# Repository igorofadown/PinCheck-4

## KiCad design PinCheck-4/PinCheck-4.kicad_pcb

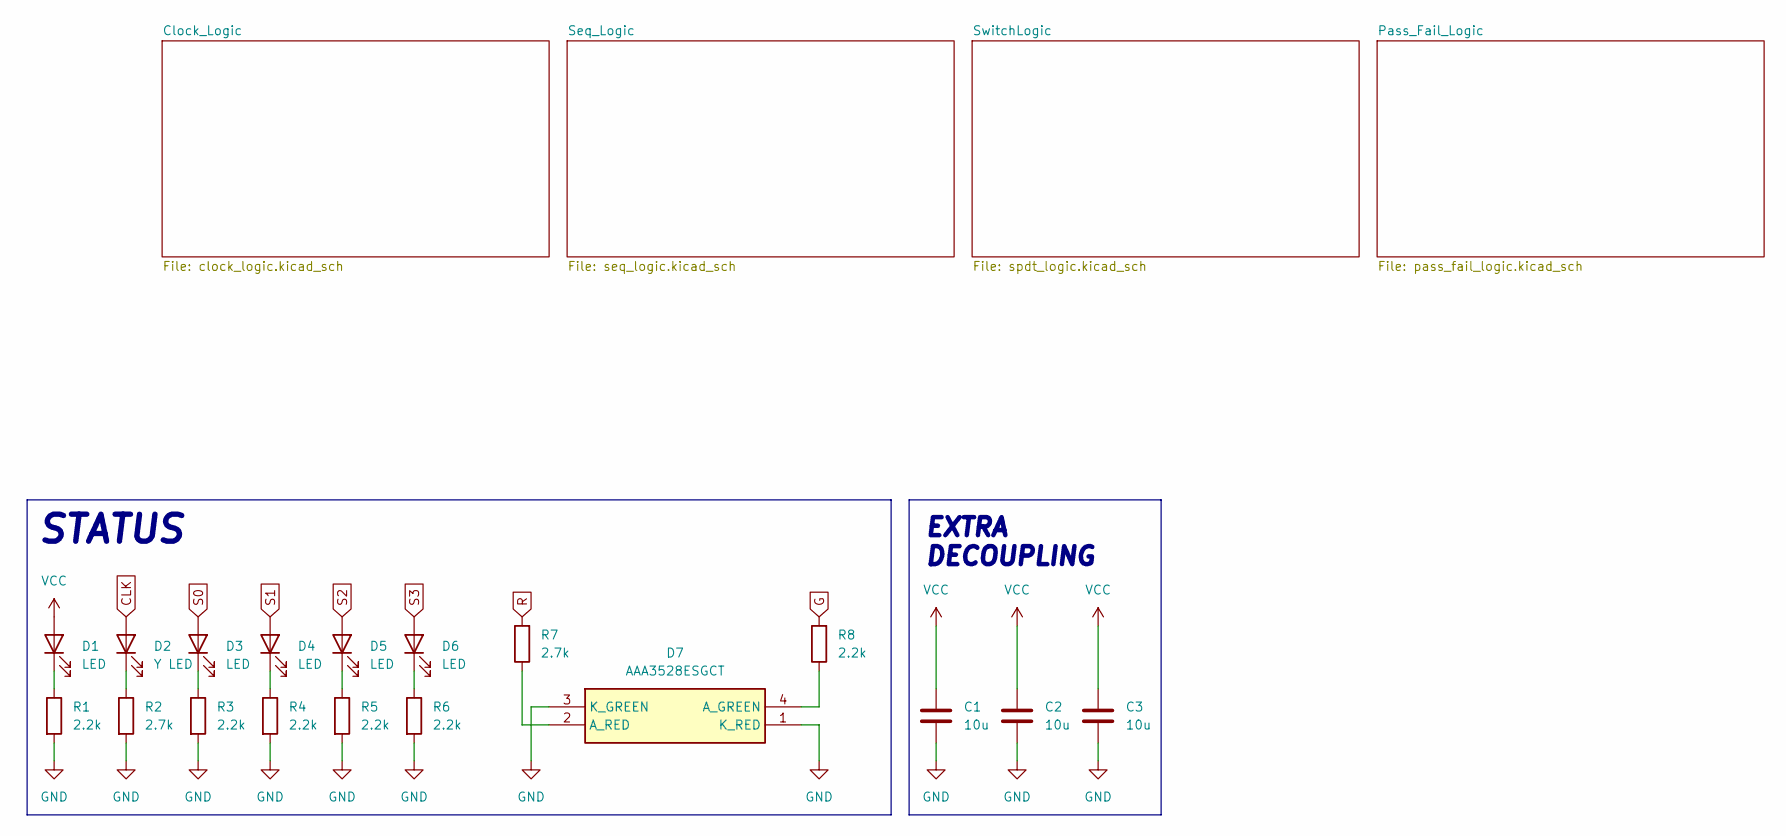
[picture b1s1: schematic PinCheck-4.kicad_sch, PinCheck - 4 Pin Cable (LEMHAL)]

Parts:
C1, C2, C3: 10u; C_0805_2012Metric
D1, D3, D4, D5, D6: LED; LED_0805_2012Metric; Manufacturer Part No KP-2012MGC
D2: Y LED; LED_0805_2012Metric; Manufacturer Part No KP-2012SECK
D7: AAA3528ESGCT; Manufacturer_Part_Number AAA3528ESGCT; Mouser Part Number 604-AAA3528ESGCT
R1, R3, R4, R5, R6, R8: 2.2k; R_0805_2012Metric; Manufacturer Part No MC01W080512K2
R2, R7: 2.7k; R_0805_2012Metric; Manufacturer Part No MCMR08X2701FTL

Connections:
CLK: D2.2 (A); also elsewhere on the board
G: R8.2; also elsewhere on the board
GND: C1.2, C2.2, C3.2, D7.1 (K_RED), D7.3 (K_GREEN), R1.2, R2.2, R3.2, R4.2, R5.2, R6.2; also elsewhere on the board
unnamed: D1.1 (K), R1.1
unnamed: D2.1 (K), R2.1
unnamed: D3.1 (K), R3.1
unnamed: D4.1 (K), R4.1
unnamed: D5.1 (K), R5.1
unnamed: D6.1 (K), R6.1
unnamed: D7.4 (A_GREEN), R8.1
unnamed: D7.2 (A_RED), R7.1
R: R7.2; also elsewhere on the board
S0: D3.2 (A); also elsewhere on the board
S1: D4.2 (A); also elsewhere on the board
S2: D5.2 (A); also elsewhere on the board
S3: D6.2 (A); also elsewhere on the board
VCC: C1.1, C2.1, C3.1, D1.2 (A); also elsewhere on the board

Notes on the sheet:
EXTRA DECOUPLING
STATUS

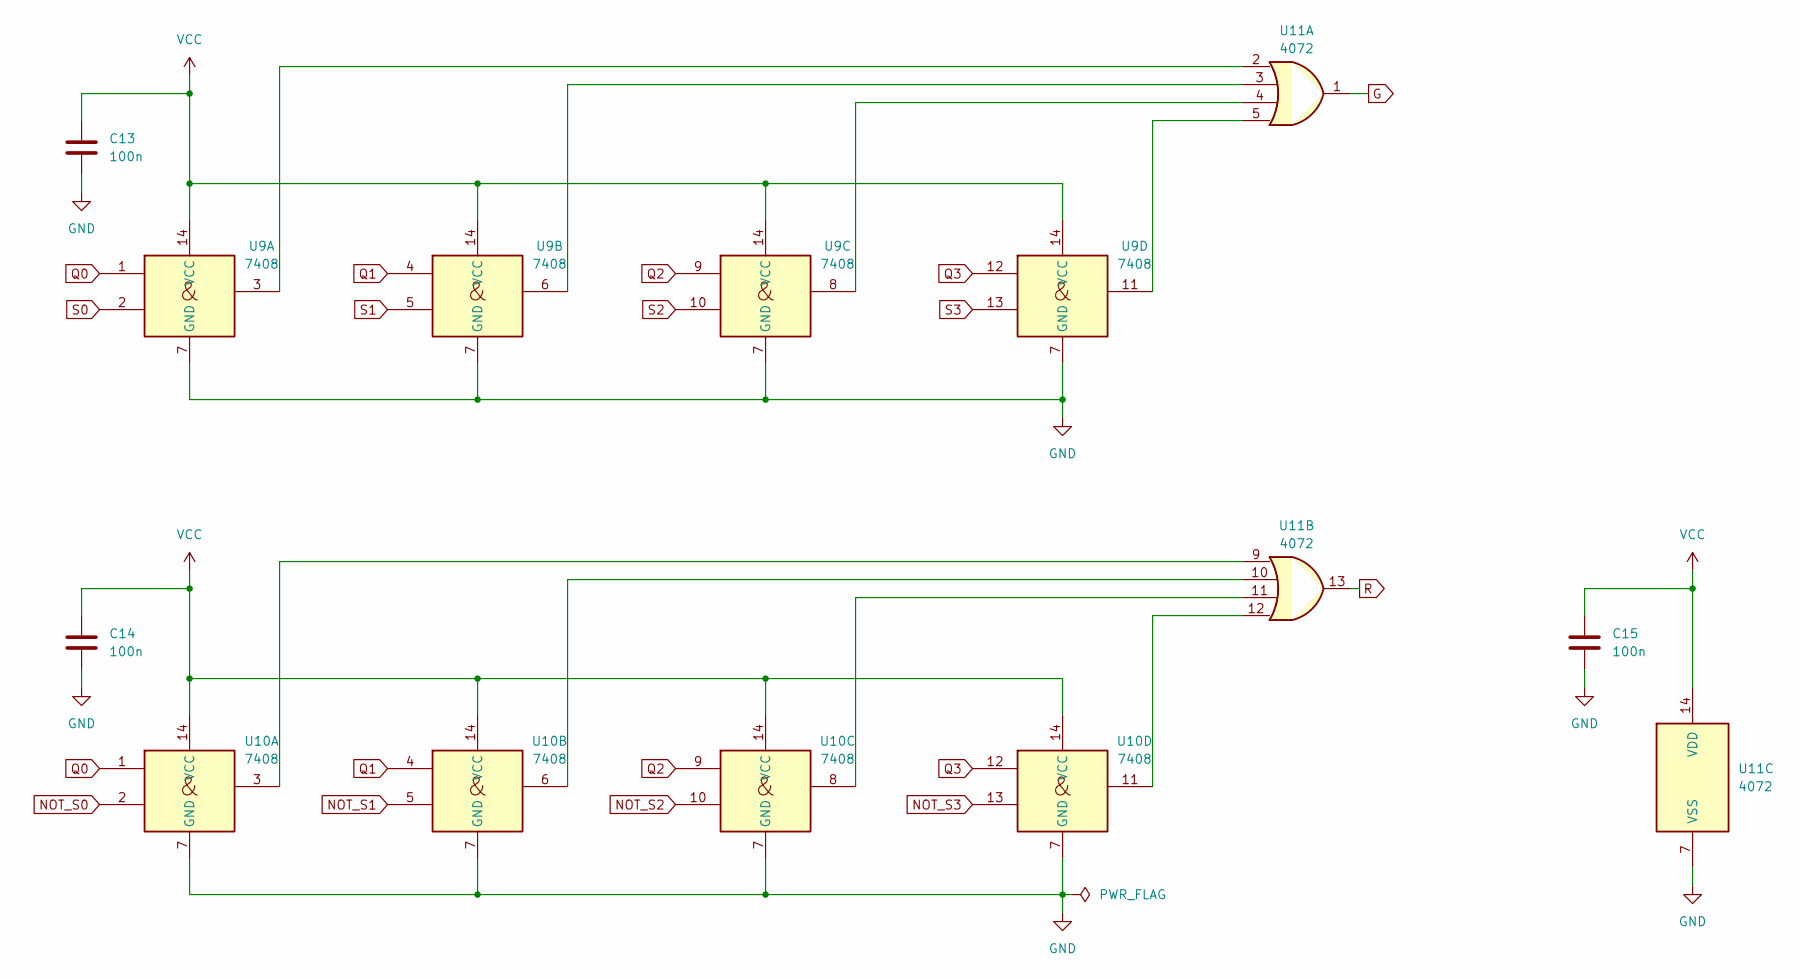
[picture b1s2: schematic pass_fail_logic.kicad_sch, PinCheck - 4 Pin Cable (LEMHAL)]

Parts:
C13, C14, C15: 100n; C_0805_2012Metric; Manufacturer Part No 0805B104K160CT
U9, U10: 7408; SOIC-14_3.9x8.7mm_P1.27mm; Manufacturer Part No 74HC08D
U11: 4072; SOIC-14_3.9x8.7mm_P1.27mm; Manufacturer Part No CD4072BM96

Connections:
G: U11.1; also elsewhere on the board
GND: C13.2, C14.2, C15.2, U9.7 (GND), U10.7 (GND), U11.7 (VSS); also elsewhere on the board
NOT_S0: U10.2; also elsewhere on the board
NOT_S1: U10.5; also elsewhere on the board
NOT_S2: U10.10; also elsewhere on the board
NOT_S3: U10.13; also elsewhere on the board
unnamed: U10.3, U11.9
unnamed: U10.6, U11.10
unnamed: U10.8, U11.11
unnamed: U10.11, U11.12
unnamed: U9.3, U11.2
unnamed: U9.6, U11.3
unnamed: U9.8, U11.4
unnamed: U9.11, U11.5
Q0: U9.1, U10.1; also elsewhere on the board
Q1: U9.4, U10.4; also elsewhere on the board
Q2: U9.9, U10.9; also elsewhere on the board
Q3: U9.12, U10.12; also elsewhere on the board
R: U11.13; also elsewhere on the board
S0: U9.2; also elsewhere on the board
S1: U9.5; also elsewhere on the board
S2: U9.10; also elsewhere on the board
S3: U9.13; also elsewhere on the board
VCC: C13.1, C14.1, C15.1, U9.14 (VCC), U10.14 (VCC), U11.14 (VDD); also elsewhere on the board

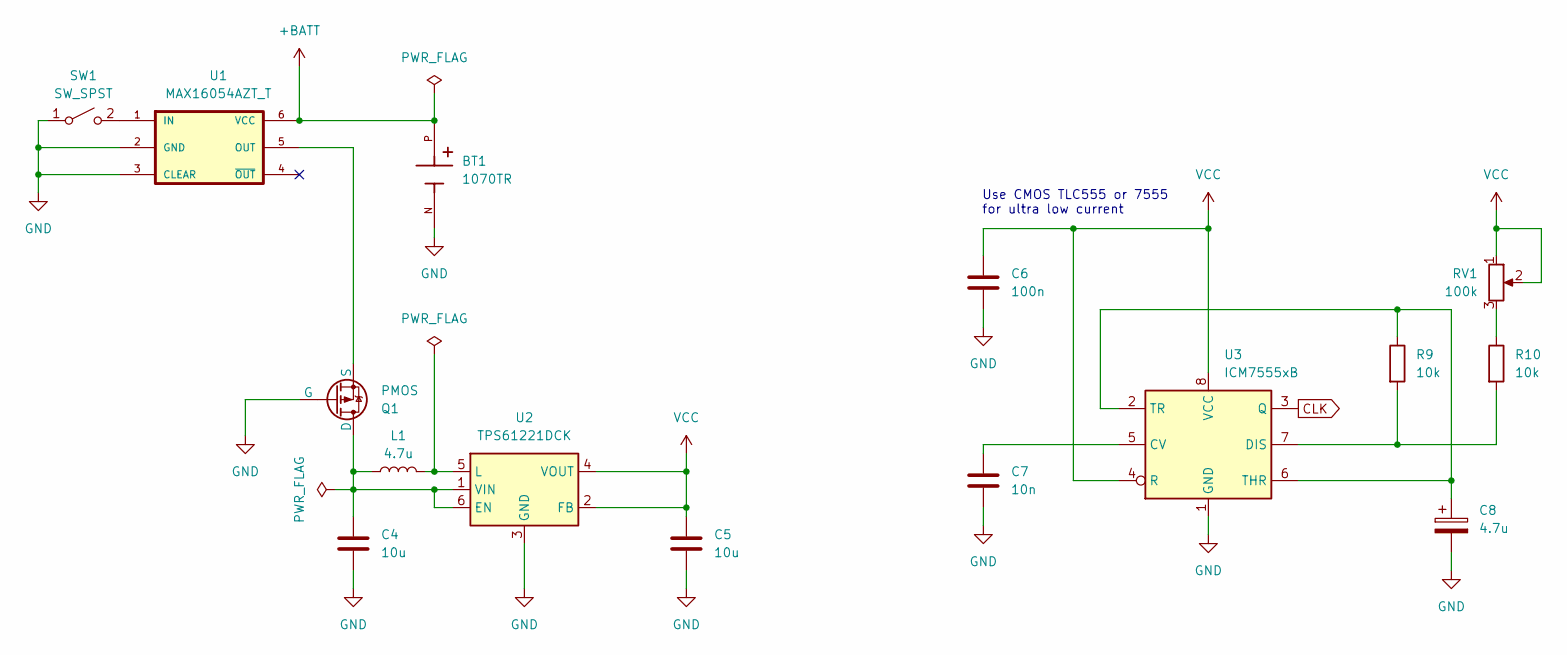
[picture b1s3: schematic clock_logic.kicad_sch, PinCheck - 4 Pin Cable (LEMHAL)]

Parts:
BT1: 1070TR; KEYSTONE_1070TR; PARTREV C
C4, C5: 10u; C_0805_2012Metric; Manufacturer Part No C2012X5R1C106M085AC
C6: 100n; C_0805_2012Metric; Manufacturer Part No 0805B104K160CT
C7: 10n; C_0805_2012Metric; Manufacturer Part No C0805S103K4RACTU
C8: 4.7u; CP_Elec_5x4.5; Manufacturer Part No EEE1EA4R7NR
L1: 4.7u; EPL3015472MLC; Manufacturer Part No EPL3015-472MLC
Q1: PMOS; SOT-323_SC-70; Manufacturer Part No AO3407A
R9, R10: 10k; R_0805_2012Metric; Manufacturer Part No CR0805-FX-1002ELF
RV1: 100k; Potentiometer_Bourns_3314G_Vertical; Manufacturer Part No 3314G-1-104E
SW1: SW_SPST; SW_SPST_PTS645Sx43SMTR92; Manufacturer Part No TS04-66-70-BK-160-SMT
U1: MAX16054AZT_T; TSOT-23-6_HandSoldering; Manufacturer Part No MAX16054AZT+T
U2: TPS61221DCK; Texas_R-PDSO-G6; Manufacturer Part No TPS61221DCKT
U3: ICM7555xB; SOIC-8_3.9x4.9mm_P1.27mm; Manufacturer Part No ICM7555ESA+T

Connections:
+BATT: BT1.P, U1.6 (VCC)
CLK: U3.3 (Q); also elsewhere on the board
GND: BT1.N, C4.2, C5.2, C6.2, C7.2, C8.2, Q1.1 (G), SW1.1 (A), U1.2 (GND), U1.3 (CLEAR), U2.3 (GND), U3.1 (GND); also elsewhere on the board
unnamed: C4.1, L1.1, Q1.3 (D), U2.1 (VIN), U2.6 (EN)
unnamed: Q1.2 (S), U1.5 (OUT)
unnamed: R10.1, RV1.3
unnamed: SW1.2 (B), U1.1 (IN)
unnamed: L1.2, U2.5 (L)
unnamed: C7.1, U3.5 (CV)
unnamed: R9.2, R10.2, U3.7 (DIS)
unnamed: C8.1, R9.1, U3.2 (TR), U3.6 (THR)
VCC: C5.1, C6.1, RV1.1, RV1.2, U2.2 (FB), U2.4 (VOUT), U3.4 (R), U3.8 (VCC); also elsewhere on the board

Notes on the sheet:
Use CMOS TLC555 or 7555 for ultra low current

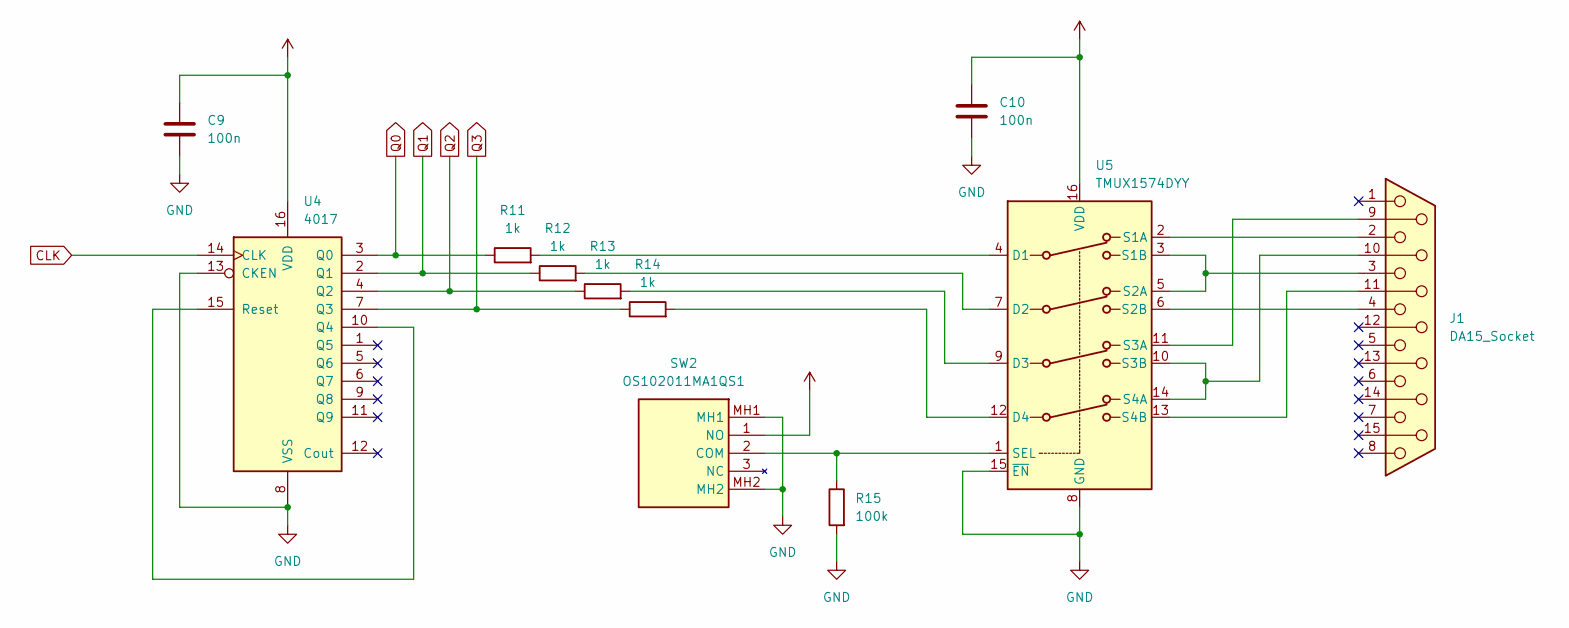
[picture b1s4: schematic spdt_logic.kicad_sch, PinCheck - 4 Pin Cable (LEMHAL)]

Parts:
C9, C10: 100n; C_0805_2012Metric; Manufacturer Part No 0805B104K160CT
J1: DA15_Socket; DSUB-15_Socket_Horizontal_P2.77x2.84mm_EdgePinOffset9.90mm_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; Manufacturer Part No MHDD15-F-T-B-S-R
R11, R12, R13, R14: 1k; R_0805_2012Metric; Manufacturer Part No MCMR08X1001FTL
R15: 100k; R_0805_2012Metric; Manufacturer Part No ERJP6WF1003V
SW2: OS102011MA1QS1; Manufacturer_Part_Number OS102011MA1QS1; Mouser Part Number N/A
U4: 4017; SOIC-16_3.9x9.9mm_P1.27mm; Manufacturer Part No CD4017BM96
U5: TMUX1574DYY; Texas_DYY0016A_TSOT-23-16_2x4.2mm_P0.5mm; Manufacturer Part No 4 Circuit IC Switch 2:1 4.5Ohm 16-SOT-2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

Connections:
CLK: U4.14 (CLK); also elsewhere on the board
GND: C9.2, C10.2, R15.2, SW2.MH1, SW2.MH2, U4.8 (VSS), U4.13 (CKEN), U5.8 (GND), U5.15 (~EN); also elsewhere on the board
unnamed: J1.9, U5.11 (S3A)
unnamed: J1.10, U5.10 (S3B), U5.14 (S4A)
unnamed: J1.11 (P111), U5.13 (S4B)
unnamed: R15.1, SW2.2 (COM), U5.1 (SEL)
unnamed: U4.10 (Q4), U4.15 (Reset)
unnamed: R11.2, U5.4 (D1)
unnamed: R12.2, U5.7 (D2)
unnamed: R13.2, U5.9 (D3)
unnamed: R14.2, U5.12 (D4)
unnamed: J1.2, U5.2 (S1A)
unnamed: J1.3, U5.3 (S1B), U5.5 (S2A)
unnamed: J1.4, U5.6 (S2B)
Q0: R11.1, U4.3 (Q0); also elsewhere on the board
Q1: R12.1, U4.2 (Q1); also elsewhere on the board
Q2: R13.1, U4.4 (Q2); also elsewhere on the board
Q3: R14.1, U4.7 (Q3); also elsewhere on the board
VCC: C9.1, C10.1, SW2.1 (NO), U4.16 (VDD), U5.16 (VDD); also elsewhere on the board

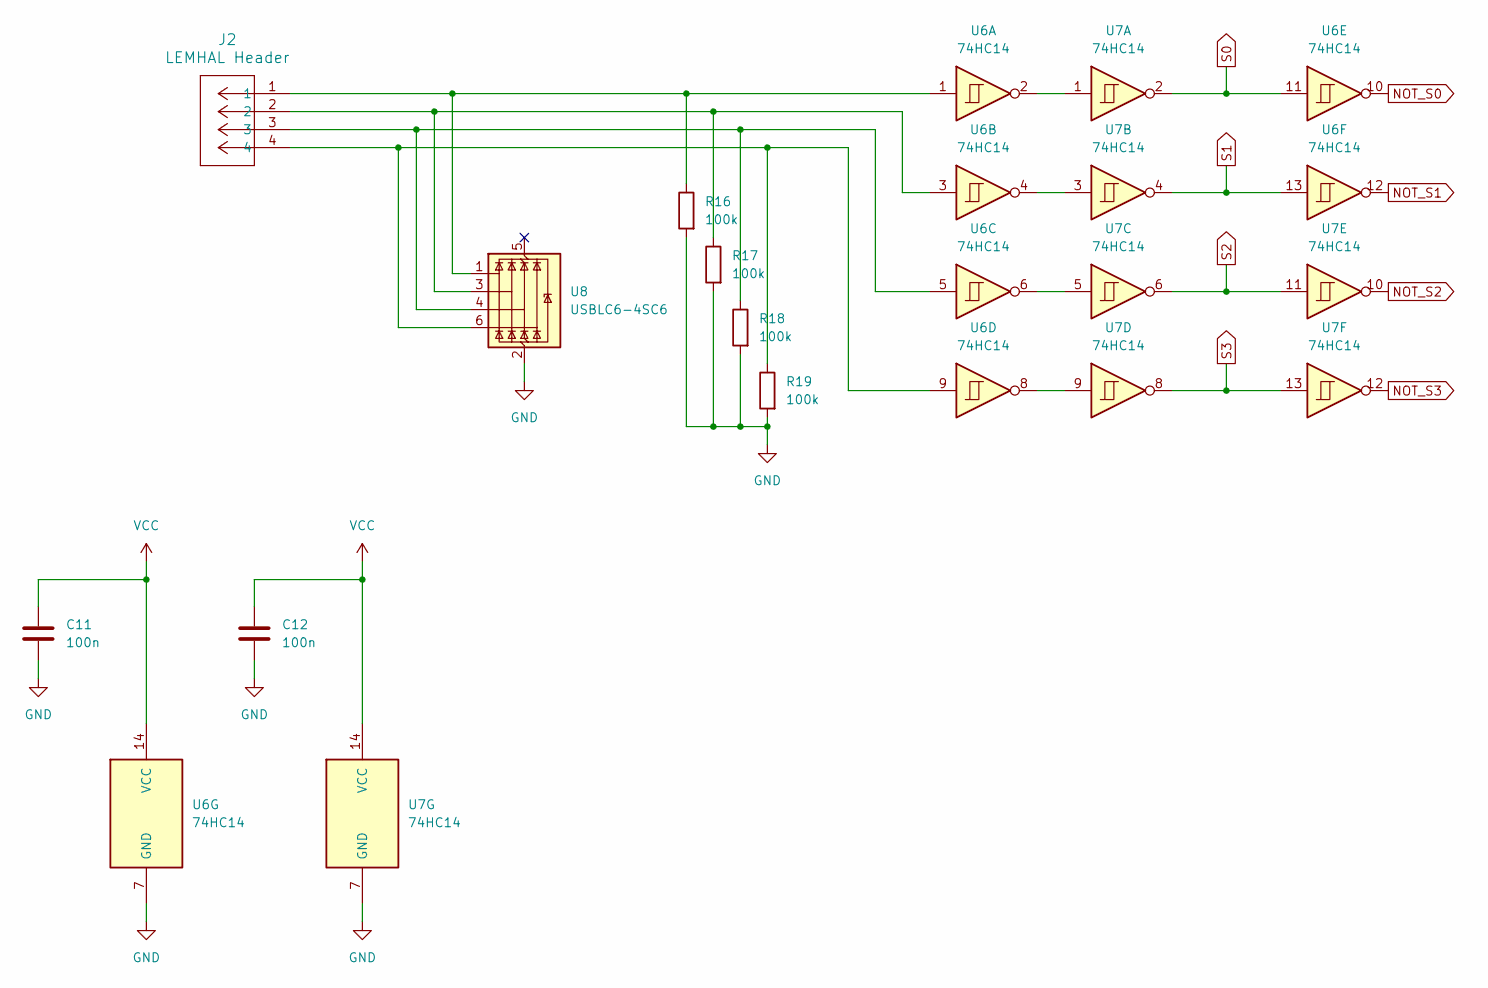
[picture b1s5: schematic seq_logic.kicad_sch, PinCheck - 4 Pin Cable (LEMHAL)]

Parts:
C11, C12: 100n; C_0805_2012Metric; Manufacturer Part No 0805B104K160CT
J2: LEMHAL Header; CONN_A-7478-04A_MOL; Manufacturer Part No 22-05-3041
R16, R17, R18, R19: 100k; R_0805_2012Metric; Manufacturer Part No ERJP6WF1003V
U6, U7: 74HC14; SOIC-14_3.9x8.7mm_P1.27mm; Manufacturer Part No 74HC14D
U8: USBLC6-4SC6; SOT-23-6; Manufacturer Part No USBLC6-4SC6

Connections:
GND: C11.2, C12.2, R16.2, R17.2, R18.2, R19.2, U6.7 (GND), U7.7 (GND), U8.2 (GND); also elsewhere on the board
NOT_S0: U6.10; also elsewhere on the board
NOT_S1: U6.12; also elsewhere on the board
NOT_S2: U7.10; also elsewhere on the board
NOT_S3: U7.12; also elsewhere on the board
unnamed: U6.2, U7.1
unnamed: U6.4, U7.3
unnamed: U6.6, U7.5
unnamed: U6.8, U7.9
unnamed: J2.1, R16.1, U6.1, U8.1 (I/O1)
unnamed: J2.2, R17.1, U6.3, U8.3 (I/O2)
unnamed: J2.3, R18.1, U6.5, U8.4 (I/O3)
unnamed: J2.4, R19.1, U6.9, U8.6 (I/O4)
S0: U6.11, U7.2; also elsewhere on the board
S1: U6.13, U7.4; also elsewhere on the board
S2: U7.6, U7.11; also elsewhere on the board
S3: U7.8, U7.13; also elsewhere on the board
VCC: C11.1, C12.1, U6.14 (VCC), U7.14 (VCC); also elsewhere on the board

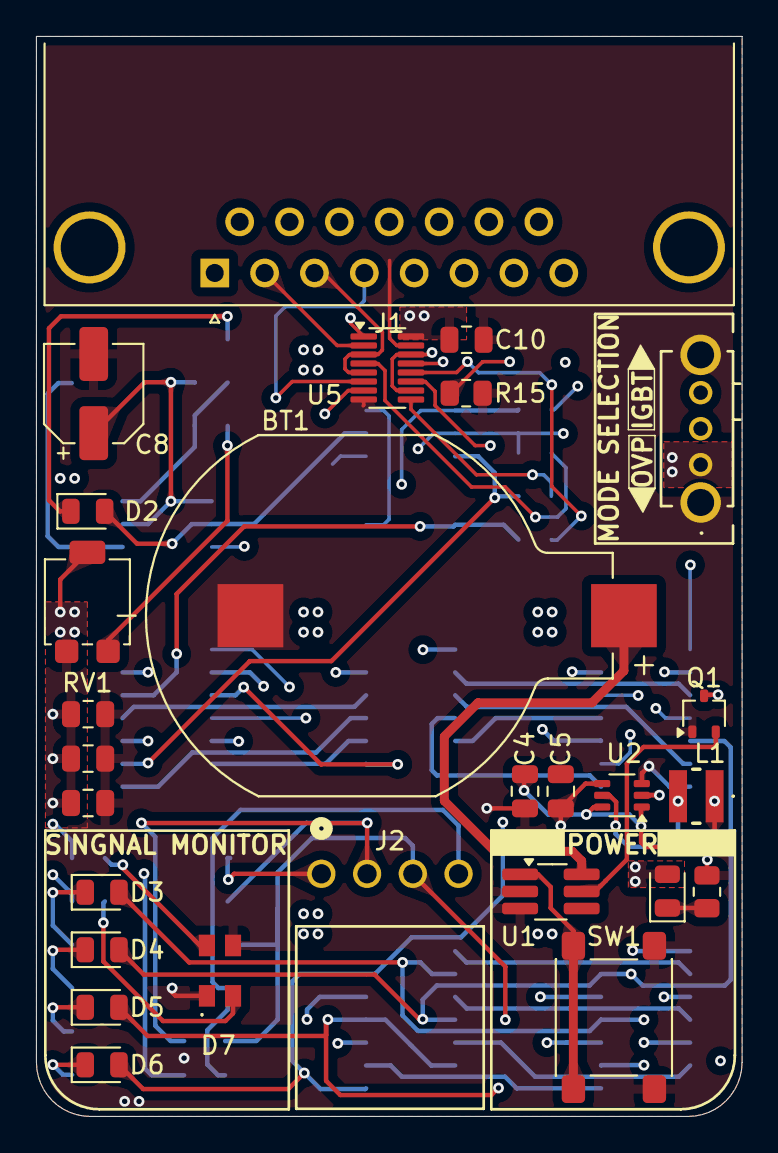
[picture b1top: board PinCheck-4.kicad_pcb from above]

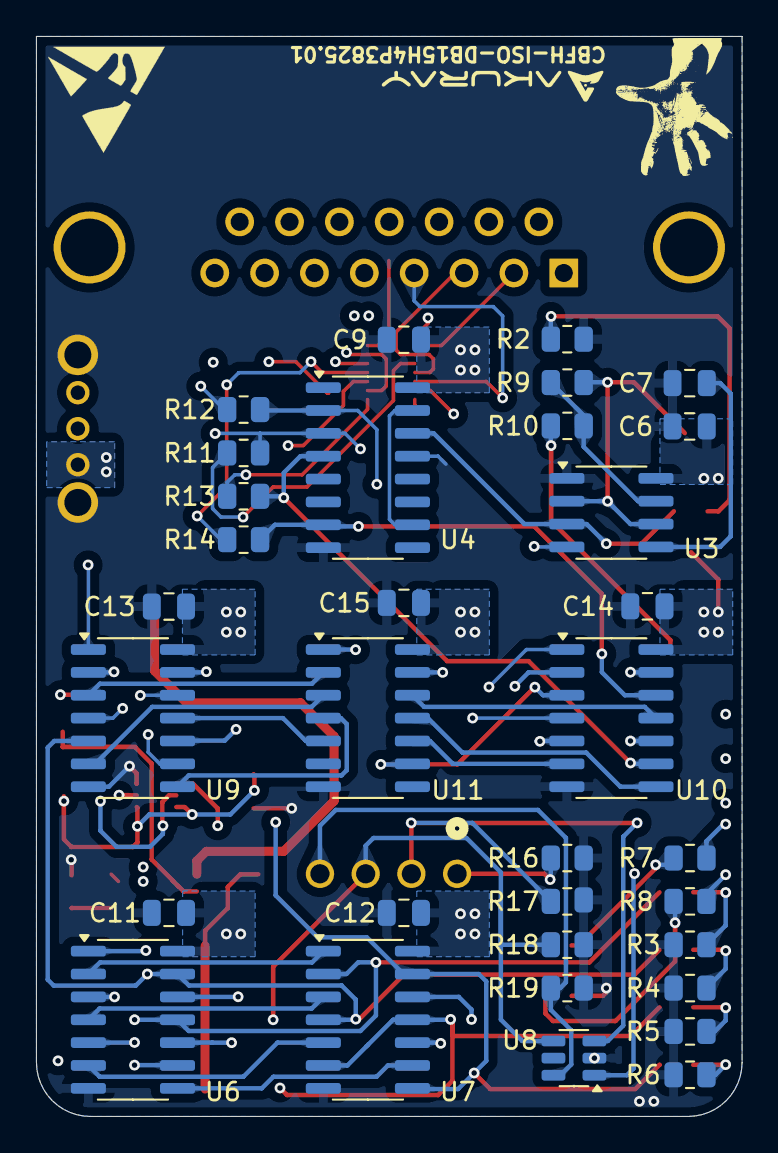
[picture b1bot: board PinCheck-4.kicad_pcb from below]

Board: 4 copper layers, 39.2 x 60.0 mm, 60 parts (33 on the bottom side), 62 nets.

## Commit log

2025-08-26 Daily sync 2025-08-26 16:39
2025-08-27 Daily sync 2025-08-27 12:04
2025-08-27 Daily sync 2025-08-27 16:57
2025-08-27 Daily sync 2025-08-27 22:21
2025-08-28 Daily sync 2025-08-28 16:55
2025-08-29 Daily sync 2025-08-29 22:48
2025-08-30 Daily sync 2025-08-30 13:49
2025-08-30 Daily sync 2025-08-30 21:30
2025-08-31 Daily sync 2025-08-31 12:14
2025-08-31 Daily sync 2025-08-31 15:53
2025-08-31 Daily sync 2025-08-31 16:37
2025-09-01 Daily sync 2025-09-01 09:07
2025-09-01 Daily sync 2025-09-01 11:59
2025-09-02 Daily sync 2025-09-02 09:54
2025-09-15 Daily sync 2025-09-15 17:00
2025-09-16 Daily sync 2025-09-16 16:52
2025-09-17 Daily sync 2025-09-17 12:09
2025-09-17 Daily sync 2025-09-17 15:01
